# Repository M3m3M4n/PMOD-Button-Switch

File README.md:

# PMOD Button-Switch

Based on [this](https://github.com/fm4dd/pmod-tslide4). Now fit within a single PMOD slot

Changes:
  - Thinner, SMD component
  - Combine slide switches to a single bit switch

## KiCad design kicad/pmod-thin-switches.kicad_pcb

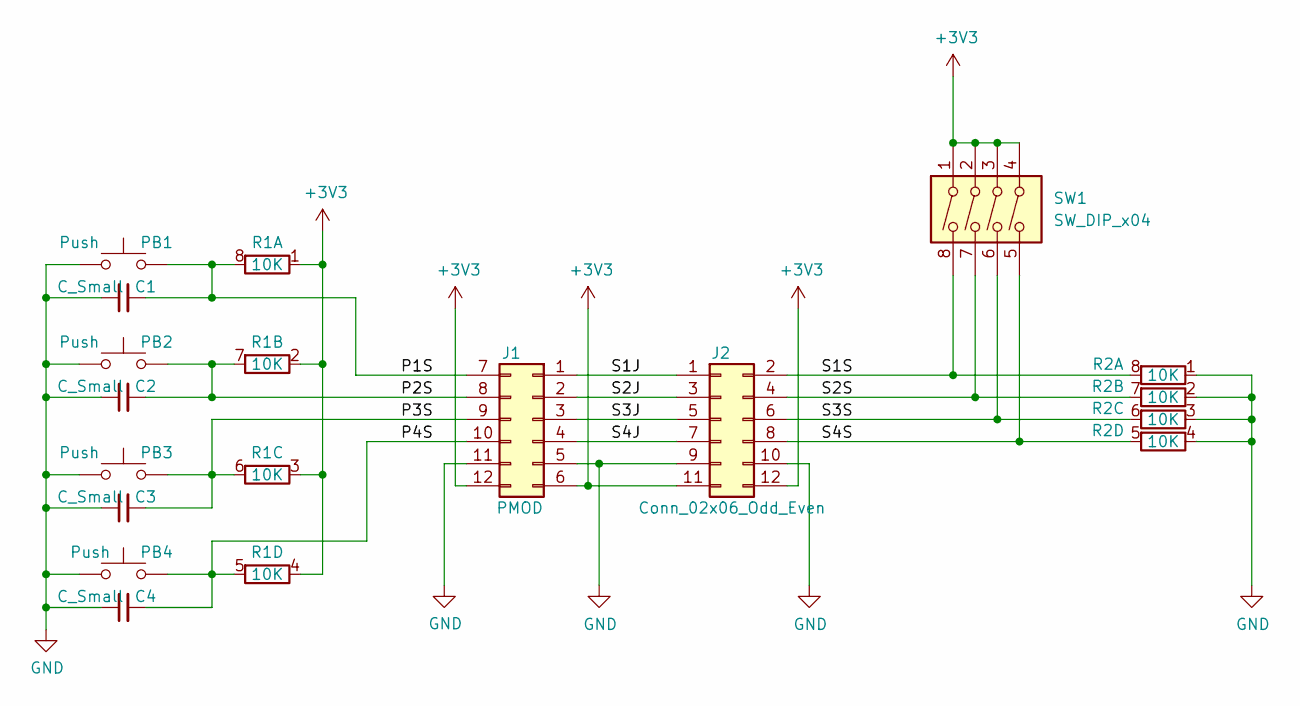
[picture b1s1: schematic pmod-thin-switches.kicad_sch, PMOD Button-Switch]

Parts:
C1, C2, C3, C4: C_Small; C_0603_1608Metric_Pad1.08x0.95mm_HandSolder
J1: PMOD; Pmod_Header_2x06_P2.54mm_Horizontal
J2: Conn_02x06_Odd_Even; PinHeader_2x06_P2.54mm_Vertical
PB1, PB2, PB3, PB4: Push; SW_PUSH_6mm_H5mm
R1, R2: 10K; R_Array_Convex_4x0603
SW1: SW_DIP_x04; SW_DIP_SPSTx04_Slide_9.78x12.34mm_W7.62mm_P2.54mm

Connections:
+3V3: J1.6, J1.12, J2.11, J2.12, R1.1 (R1.1), R1.2 (R2.1), R1.3 (R3.1), R1.4 (R4.1), SW1.1, SW1.2, SW1.3, SW1.4
/P1S: C1.2, J1.7, PB1.2, R1.8 (R1.2)
/P2S: C2.2, J1.8, PB2.2, R1.7 (R2.2)
/P3S: C3.2, J1.9, PB3.2, R1.6 (R3.2)
/P4S: C4.2, J1.10, PB4.2, R1.5 (R4.2)
/S1J: J1.1, J2.1
/S1S: J2.2, R2.8 (R1.2), SW1.8
/S2J: J1.2, J2.3
/S2S: J2.4, R2.7 (R2.2), SW1.7
/S3J: J1.3, J2.5
/S3S: J2.6, R2.6 (R3.2), SW1.6
/S4J: J1.4, J2.7
/S4S: J2.8, R2.5 (R4.2), SW1.5
GND: C1.1, C2.1, C3.1, C4.1, J1.5, J1.11, J2.9, J2.10, PB1.1, PB2.1, PB3.1, PB4.1, R2.1 (R1.1), R2.2 (R2.1), R2.3 (R3.1), R2.4 (R4.1)

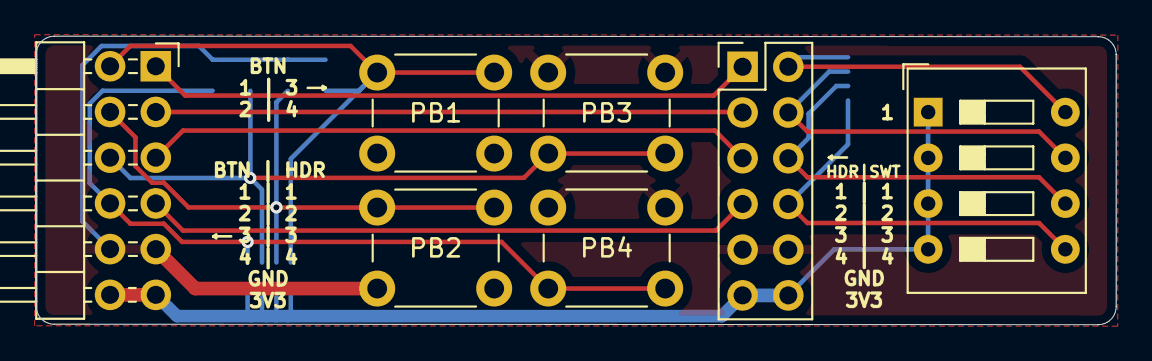
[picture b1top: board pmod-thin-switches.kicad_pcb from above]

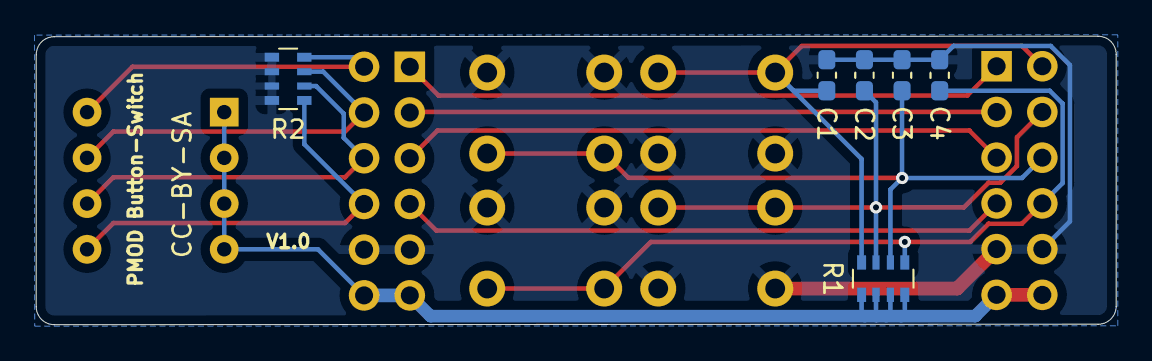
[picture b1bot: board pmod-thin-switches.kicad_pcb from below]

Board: 2 copper layers, 60.0 x 16.0 mm, 13 parts (6 on the bottom side), 14 nets.

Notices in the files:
kicad/pmod-thin-switches.kicad_pcb:
CC-BY-SA
